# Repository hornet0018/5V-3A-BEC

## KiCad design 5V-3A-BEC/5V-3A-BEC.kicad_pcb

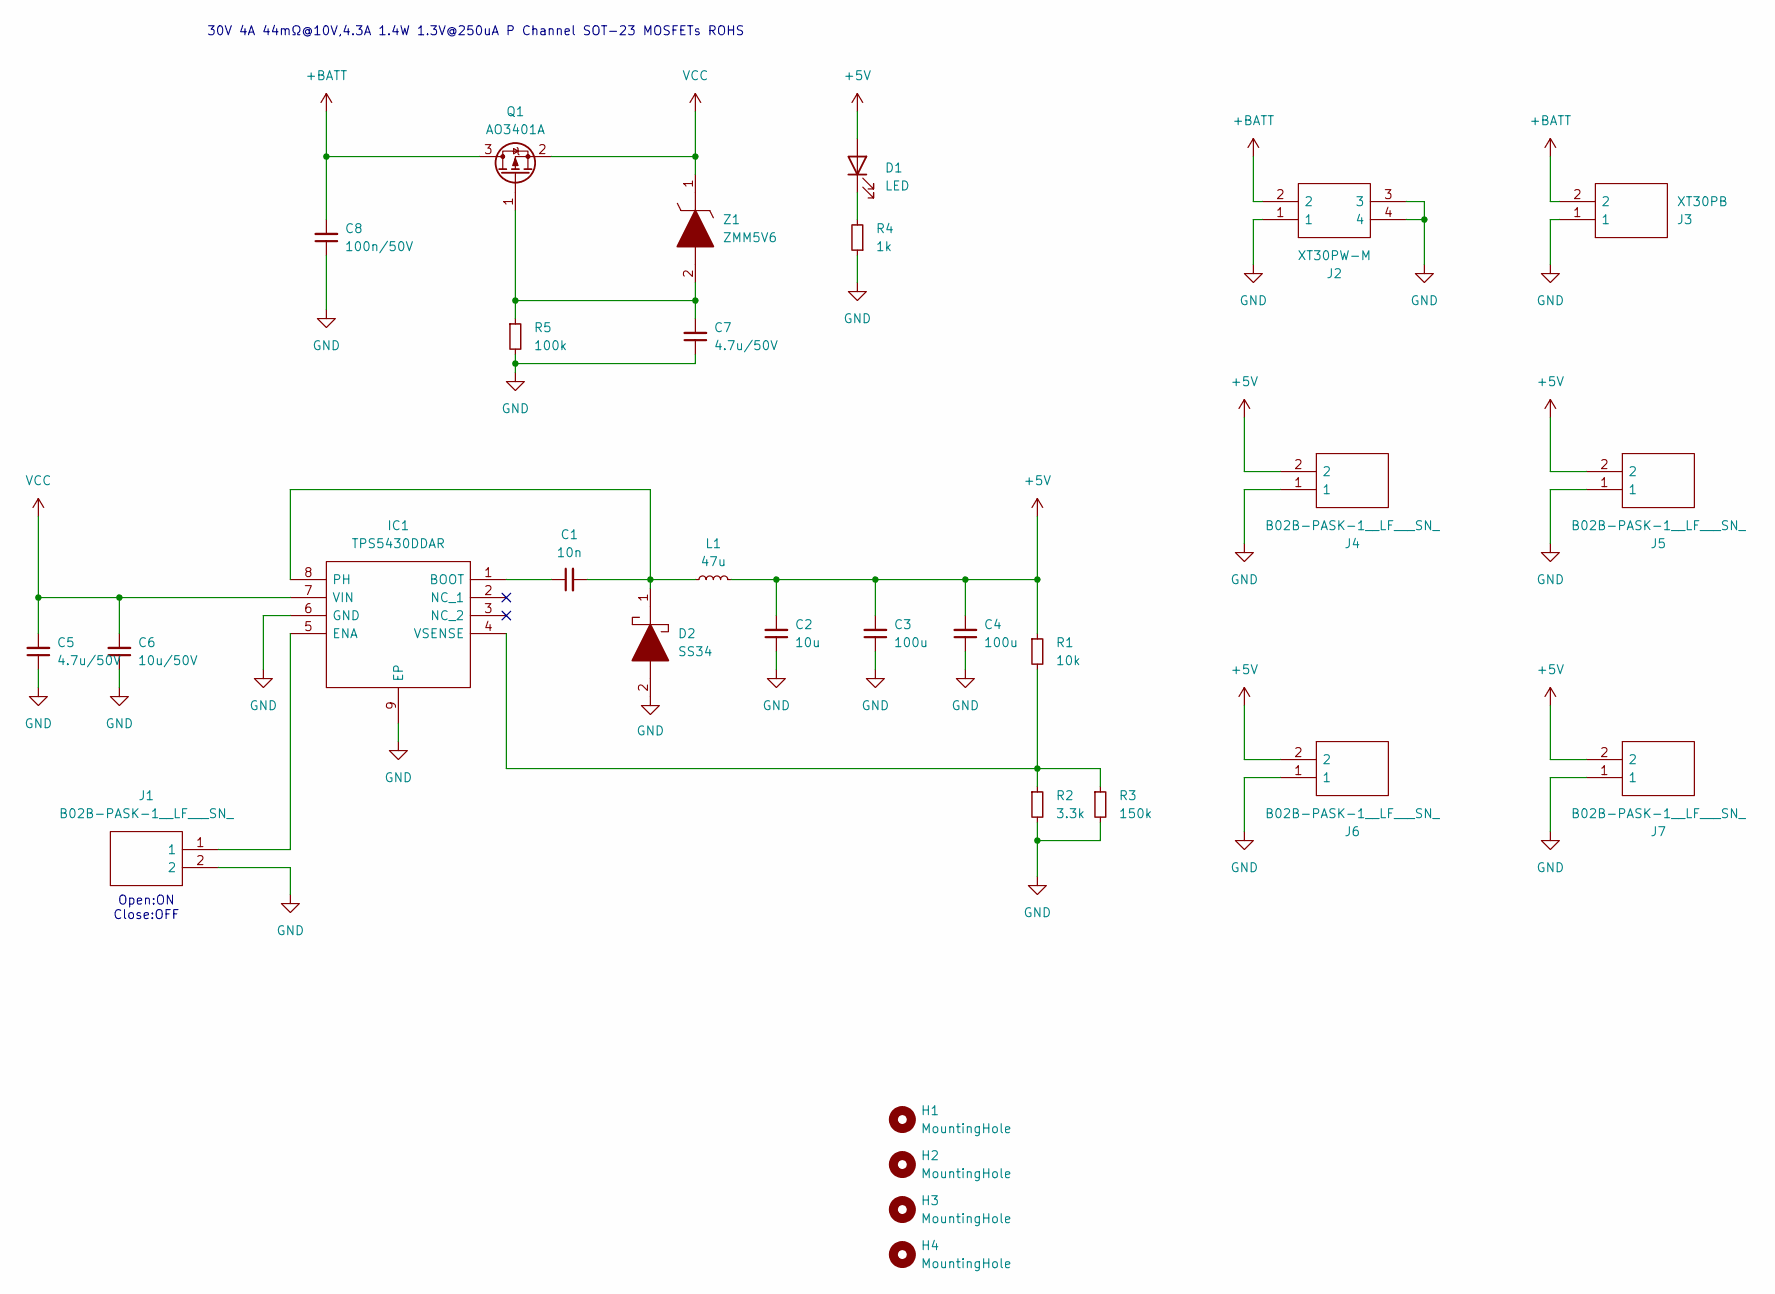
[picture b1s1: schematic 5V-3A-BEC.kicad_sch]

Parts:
C1: 10n; C_0603_1608Metric_Pad1.08x0.95mm_HandSolder
C2: 10u; C_0805_2012Metric_Pad1.18x1.45mm_HandSolder
C3, C4: 100u; C_1206_3216Metric_Pad1.33x1.80mm_HandSolder
C5, C7: 4.7u/50V; C_1206_3216Metric_Pad1.33x1.80mm_HandSolder
C6: 10u/50V; C_0805_2012Metric_Pad1.18x1.45mm_HandSolder
C8: 100n/50V; C_0603_1608Metric_Pad1.08x0.95mm_HandSolder
D1: LED; LED_0603_1608Metric_Pad1.05x0.95mm_HandSolder
D2: SS34; DIOM5436X244N; Manufacturer_Part_Number SS34
H1, H2, H3, H4: MountingHole; MountingHole_3.2mm_M3_Pad_Via
IC1: TPS5430DDAR; SOIC127P600X170-9N; Manufacturer_Part_Number TPS5430DDAR; Mouser Part Number 595-TPS5430DDAR
J1, J4, J5, J6, J7: B02B-PASK-1__LF___SN_; B02BPASK1LFSN; Manufacturer_Part_Number B02B-PASK-1 (LF) (SN)
J2: XT30PW-M; XT30PWM; Manufacturer_Part_Number XT30PW-M
J3: XT30PB; Manufacturer_Part_Number XT30PB
L1: 47u; L_Sunlord_MWSA1004S
Q1: AO3401A; SOT-23
R1: 10k; R_0603_1608Metric_Pad0.98x0.95mm_HandSolder
R2: 3.3k; R_0603_1608Metric_Pad0.98x0.95mm_HandSolder
R3: 150k; R_0603_1608Metric_Pad0.98x0.95mm_HandSolder
R4: 1k; R_0603_1608Metric_Pad0.98x0.95mm_HandSolder
R5: 100k; R_0603_1608Metric_Pad0.98x0.95mm_HandSolder
Z1: ZMM5V6; Manufacturer_Part_Number ZMM5V6

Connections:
+5V: C2.2, C3.2, C4.2, D1.2 (A), J4.2, J5.2, J6.2, J7.2, L1.2, R1.1
+BATT: C8.2, J2.2, J3.2, Q1.3 (D)
GND: C2.1, C3.1, C4.1, C5.1, C6.1, C7.1, C8.1, D2.2, IC1.6 (GND), IC1.9 (EP), J1.2, J2.1, J2.3, J2.4, J3.1, J4.1, J5.1, J6.1, J7.1, R2.2, R3.2, R4.1, R5.2
unnamed: D1.1 (K), R4.2
unnamed: C1.1, IC1.1 (BOOT)
unnamed: IC1.5 (ENA), J1.1
unnamed: C1.2, D2.1, IC1.8 (PH), L1.1
unnamed: IC1.4 (VSENSE), R1.2, R2.1, R3.1
unnamed: C7.2, Q1.1 (G), R5.1, Z1.2
VCC: C5.2, C6.2, IC1.7 (VIN), Q1.2 (S), Z1.1

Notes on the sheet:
Open:ON Close:OFF
30V 4A 44mΩ@10V,4.3A 1.4W 1.3V@250uA P Channel SOT-23 MOSFETs ROHS

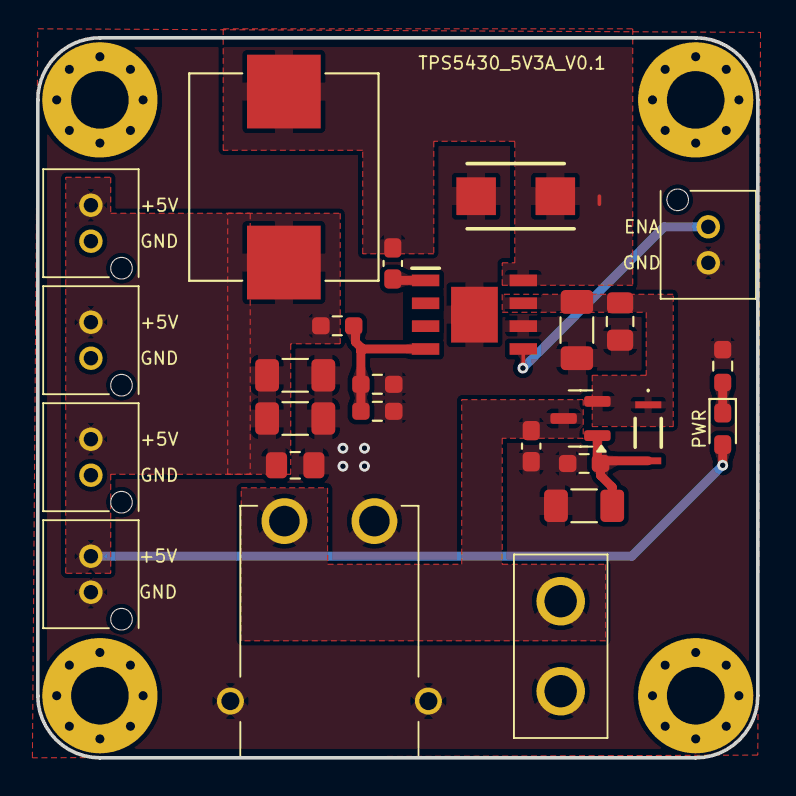
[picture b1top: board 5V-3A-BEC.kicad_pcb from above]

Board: 6 copper layers, 40.0 x 40.0 mm, 30 parts (0 on the bottom side), 10 nets.

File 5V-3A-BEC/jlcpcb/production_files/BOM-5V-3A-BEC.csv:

Comment,Designator,Footprint,LCSC
100n/50V,C8,C_0603_1608Metric_Pad1.08x0.95mm_HandSolder,C14663
100u,"C3,C4",C_1206_3216Metric_Pad1.33x1.80mm_HandSolder,C15008
AO3401A,Q1,SOT-23,C15127
1k,R4,R_0603_1608Metric_Pad0.98x0.95mm_HandSolder,C21190
150k,R3,R_0603_1608Metric_Pad0.98x0.95mm_HandSolder,C22807
LED,D1,LED_0603_1608Metric_Pad1.05x0.95mm_HandSolder,C2286
3.3k,R2,R_0603_1608Metric_Pad0.98x0.95mm_HandSolder,C22978
100k,R5,R_0603_1608Metric_Pad0.98x0.95mm_HandSolder,C25803
10k,R1,R_0603_1608Metric_Pad0.98x0.95mm_HandSolder,C25804
ZMM5V6,Z1,ZMM5V6,C2891745
4.7u/50V,"C5,C7",C_1206_3216Metric_Pad1.33x1.80mm_HandSolder,C29823
47u,L1,L_Sunlord_MWSA1004S,C408491
10u,"C2,C6",C_0805_2012Metric_Pad1.18x1.45mm_HandSolder,C440198
10n,C1,C_0603_1608Metric_Pad1.08x0.95mm_HandSolder,C57112
SS34,D2,DIOM5436X244N,C8678
TPS5430DDAR,IC1,SOIC127P600X170-9N,C9864
B02B-PASK-1__LF___SN_,J1,B02BPASK1LFSN,
B02B-PASK-1__LF___SN_,J6,B02BPASK1LFSN,
B02B-PASK-1__LF___SN_,J5,B02BPASK1LFSN,
B02B-PASK-1__LF___SN_,J7,B02BPASK1LFSN,
XT30PW-M,J2,XT30PWM,
XT30PB,J3,XT30PB,
B02B-PASK-1__LF___SN_,J4,B02BPASK1LFSN,

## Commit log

2024-05-09 v0.1
